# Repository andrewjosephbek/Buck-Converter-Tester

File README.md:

PCB and BOM for a Bed-of-Nails (pogo pin) tester for [Buck Converter](https://github.com/andrewjosephbek/Buck-Converter).

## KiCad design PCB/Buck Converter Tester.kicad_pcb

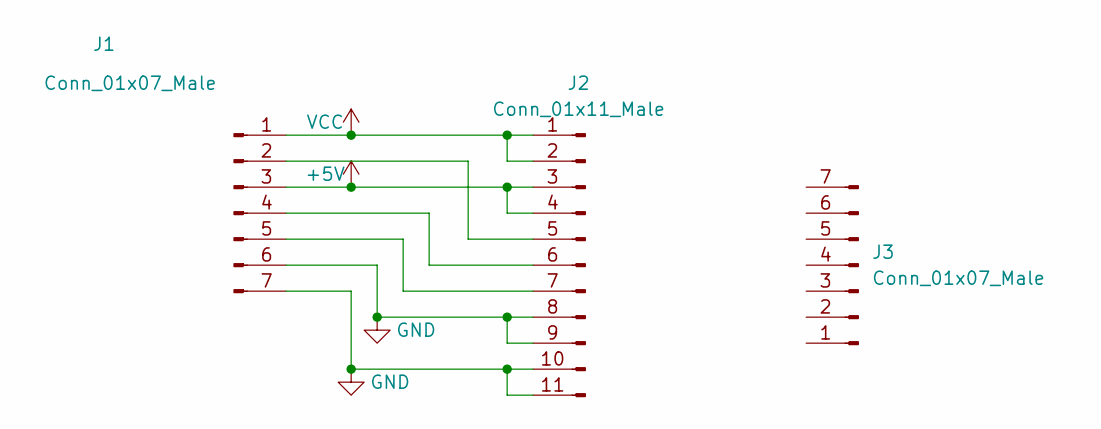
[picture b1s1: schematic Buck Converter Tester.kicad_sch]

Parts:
J1: Conn_01x07_Male; Buck Converter - Pogo Pin Solder Pads
J2: Conn_01x11_Male
J3: Conn_01x07_Male; Buck Converter - Pogo Pin Holes

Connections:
+5V: J1.3, J2.3, J2.4
GND: J1.6, J1.7, J2.8, J2.9, J2.10, J2.11
unnamed: J1.2, J2.5
unnamed: J1.4, J2.6
unnamed: J1.5, J2.7
VCC: J1.1, J2.1, J2.2

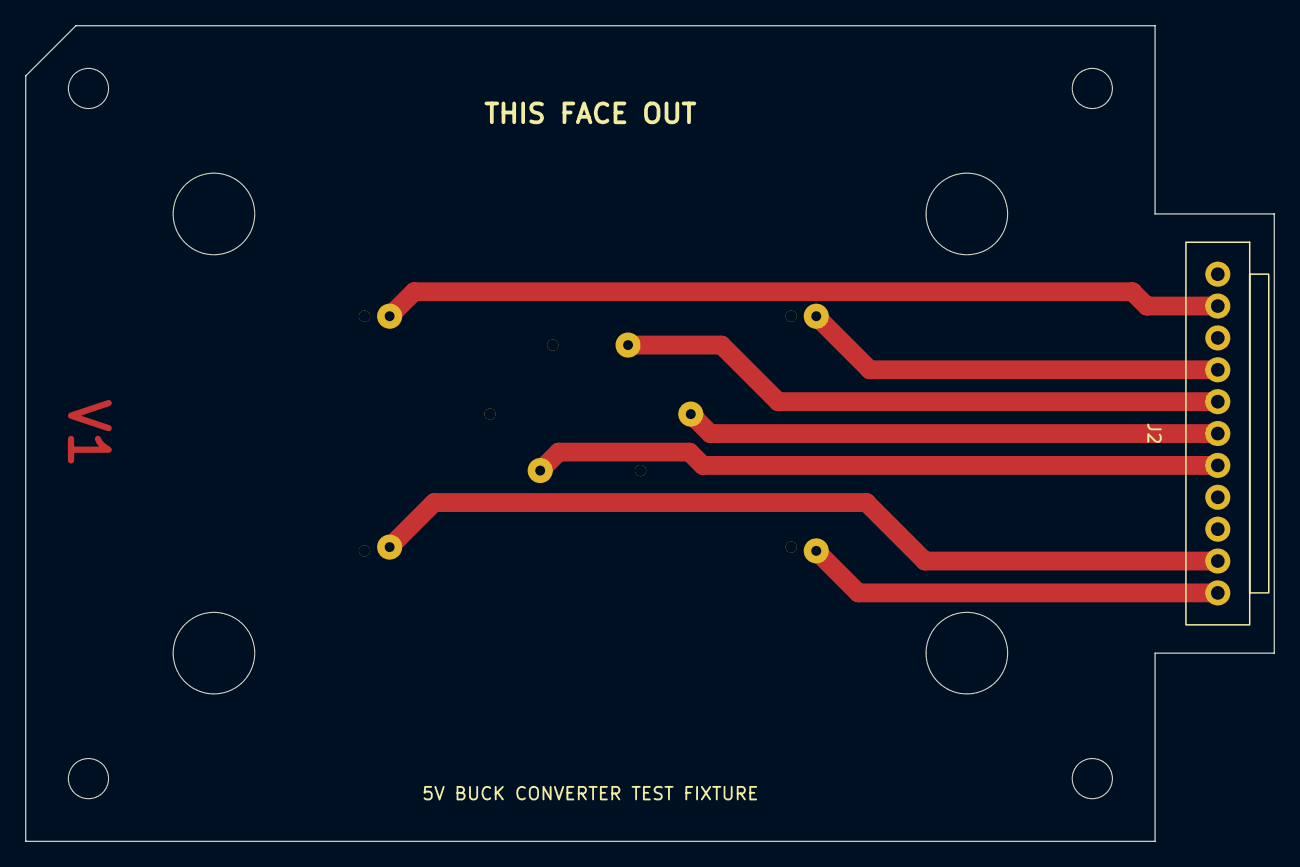
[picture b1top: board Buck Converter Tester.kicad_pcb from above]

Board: 2 copper layers, 99.5 x 65.0 mm, 3 parts (1 on the bottom side), 6 nets.

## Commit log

2026-01-12 Organized files
2026-02-18 images
